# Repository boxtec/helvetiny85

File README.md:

# helvetiny85 and helvetiny85 3.3 V

here you can find the Board Helvetiny85 (Files: HelveTiny_1.0.brd,HelveTiny_1.0.sch) and the Board Helvetiny 85 3.3 Volt (Files: HelveTiny85_3.3V.brd, HelveTiny85_3.3V.sch).
Now we have also a Fritzing Part File you can directly work with the Helvetiny85 in Fritzing.

# Kits
If you would like to buy our kits.
Helvetiny85:          http://shop.boxtec.ch/helvetiny85-kit-p-42657.html
Helvetiny85 3.3 Volt: https://shop.boxtec.ch/helvetiny85-kit-33v-p-42931.html

# Documentation
Helvetiny85:          http://playground.boxtec.ch/doku.php/arduino/attinyusb/helvetiny85
Helvetiny85 3.3 Volt: https://playground.boxtec.ch/doku.php/arduino/attinyusb/helvetiny85_3.3_v

# Tutorials
http://playground.boxtec.ch/doku.php/arduino/attinyusb/helvetiny85/tutorials

# Support Thread
http://forum.boxtec.ch/index.php/topic,3162.0.html

Have fun.
Dinoi

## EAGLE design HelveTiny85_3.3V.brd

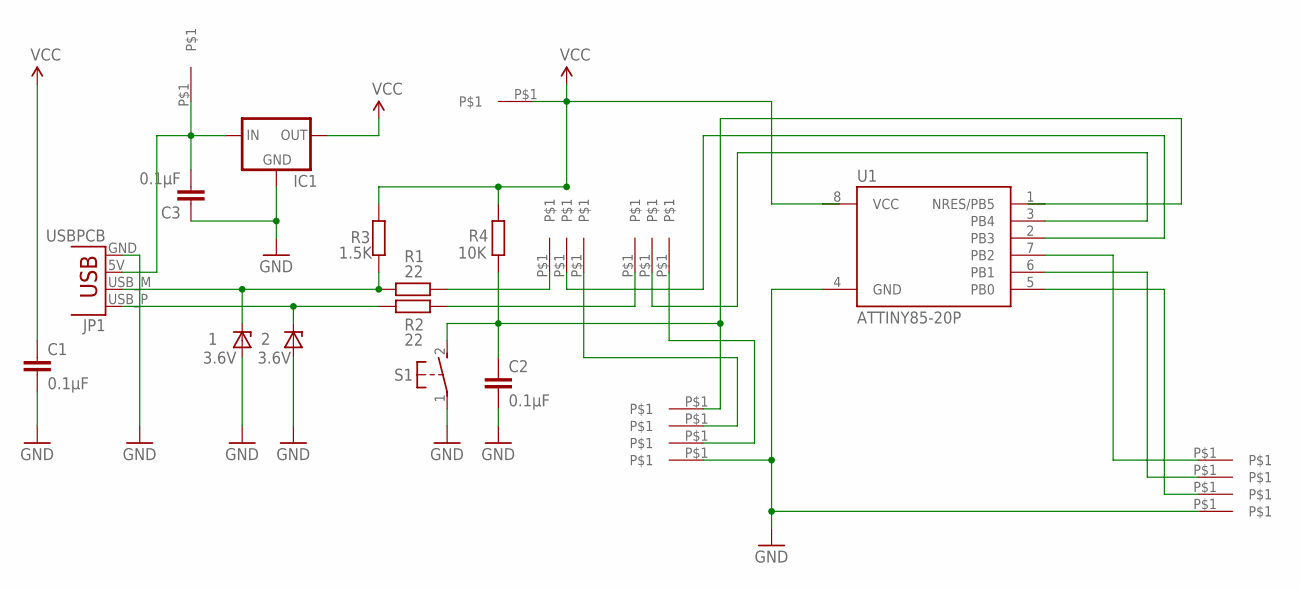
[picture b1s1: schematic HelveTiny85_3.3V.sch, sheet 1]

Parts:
1, 2: 3.6V; ZDIO-7.5
C1, C2, C3: 0.1μF; C025-024X044
IC1: MCP1700TRI; TO92
JP1: USBPCB; USB-A-PCB
R1, R2: 22; 0207/7
R3: 1.5K; 0207/7
R4: 10K; 0207/7
S1: S3; DTS-3
TP1, TP2, TP3, TP4, TP5, TP6, TP7, TP8, TP29, TP30, TP31, TP32, TP33, TP34, TP35, TP36: FLOWERPIN
U1: ATTINY85-20P; PDIP08_300MIL

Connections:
GND: 1.A, 2.A, C1.2, C2.2, C3.1, IC1.1 (GND), JP1.GND, S1.1, TP7.P$1, TP32.P$1, U1.4 (GND)
unnamed: R1.2, TP2.P$1
unnamed: TP1.P$1, TP3.P$1
unnamed: TP6.P$1, TP31.P$1
unnamed: R2.2, TP4.P$1
PB0: TP35.P$1, U1.5 (PB0)
PB1: TP34.P$1, U1.6 (PB1)
PB2: TP33.P$1, U1.7 (PB2)
RESET: C2.1, R4.1, S1.2, TP29.P$1, U1.1 (NRES/PB5)
USB-IN-M: 1.C, JP1.USB_M (D-), R1.1, R3.1
USB-IN-P: 2.C, JP1.USB_P (D+), R2.1
USB-M: TP30.P$1, U1.2 (PB3)
USB-P: TP5.P$1, U1.3 (PB4)
VCC: C1.1, IC1.3 (OUT), R3.2, R4.2, TP36.P$1, U1.8 (VCC)
VIN: C3.2, IC1.2 (IN), JP1.5V (VBUS), TP8.P$1

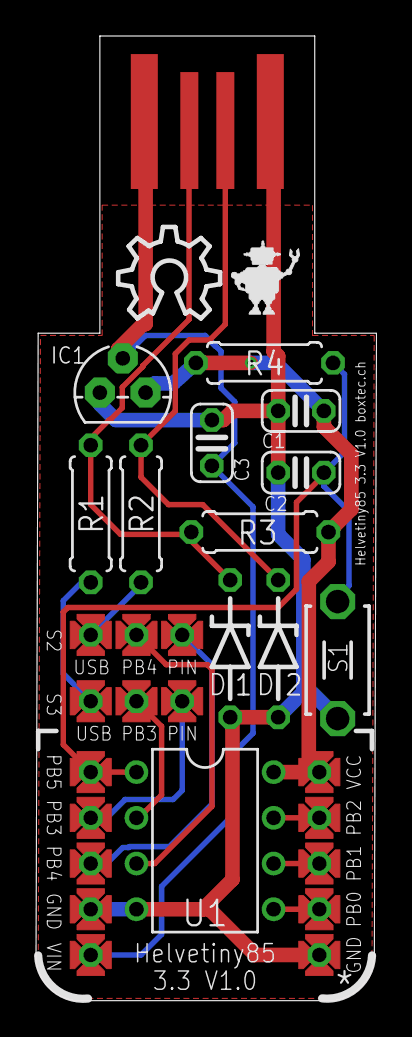
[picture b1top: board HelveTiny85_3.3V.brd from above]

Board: 2 copper layers, 18.9 x 53.6 mm, 30 parts (0 on the bottom side), 15 nets.

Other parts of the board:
U$1: OSHW_10X200_NOTEXT

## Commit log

2016-09-09 Initial git import
2017-10-06 little changes in Fritzing Part
2018-08-15 Helvetiny85 3.3Volt

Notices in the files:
parts and their libraries:
SparkFun-Connectors: Licensing: Creative Commons ShareAlike 4.0 International - https://creativecommons.org/licenses/by-sa/4.0
